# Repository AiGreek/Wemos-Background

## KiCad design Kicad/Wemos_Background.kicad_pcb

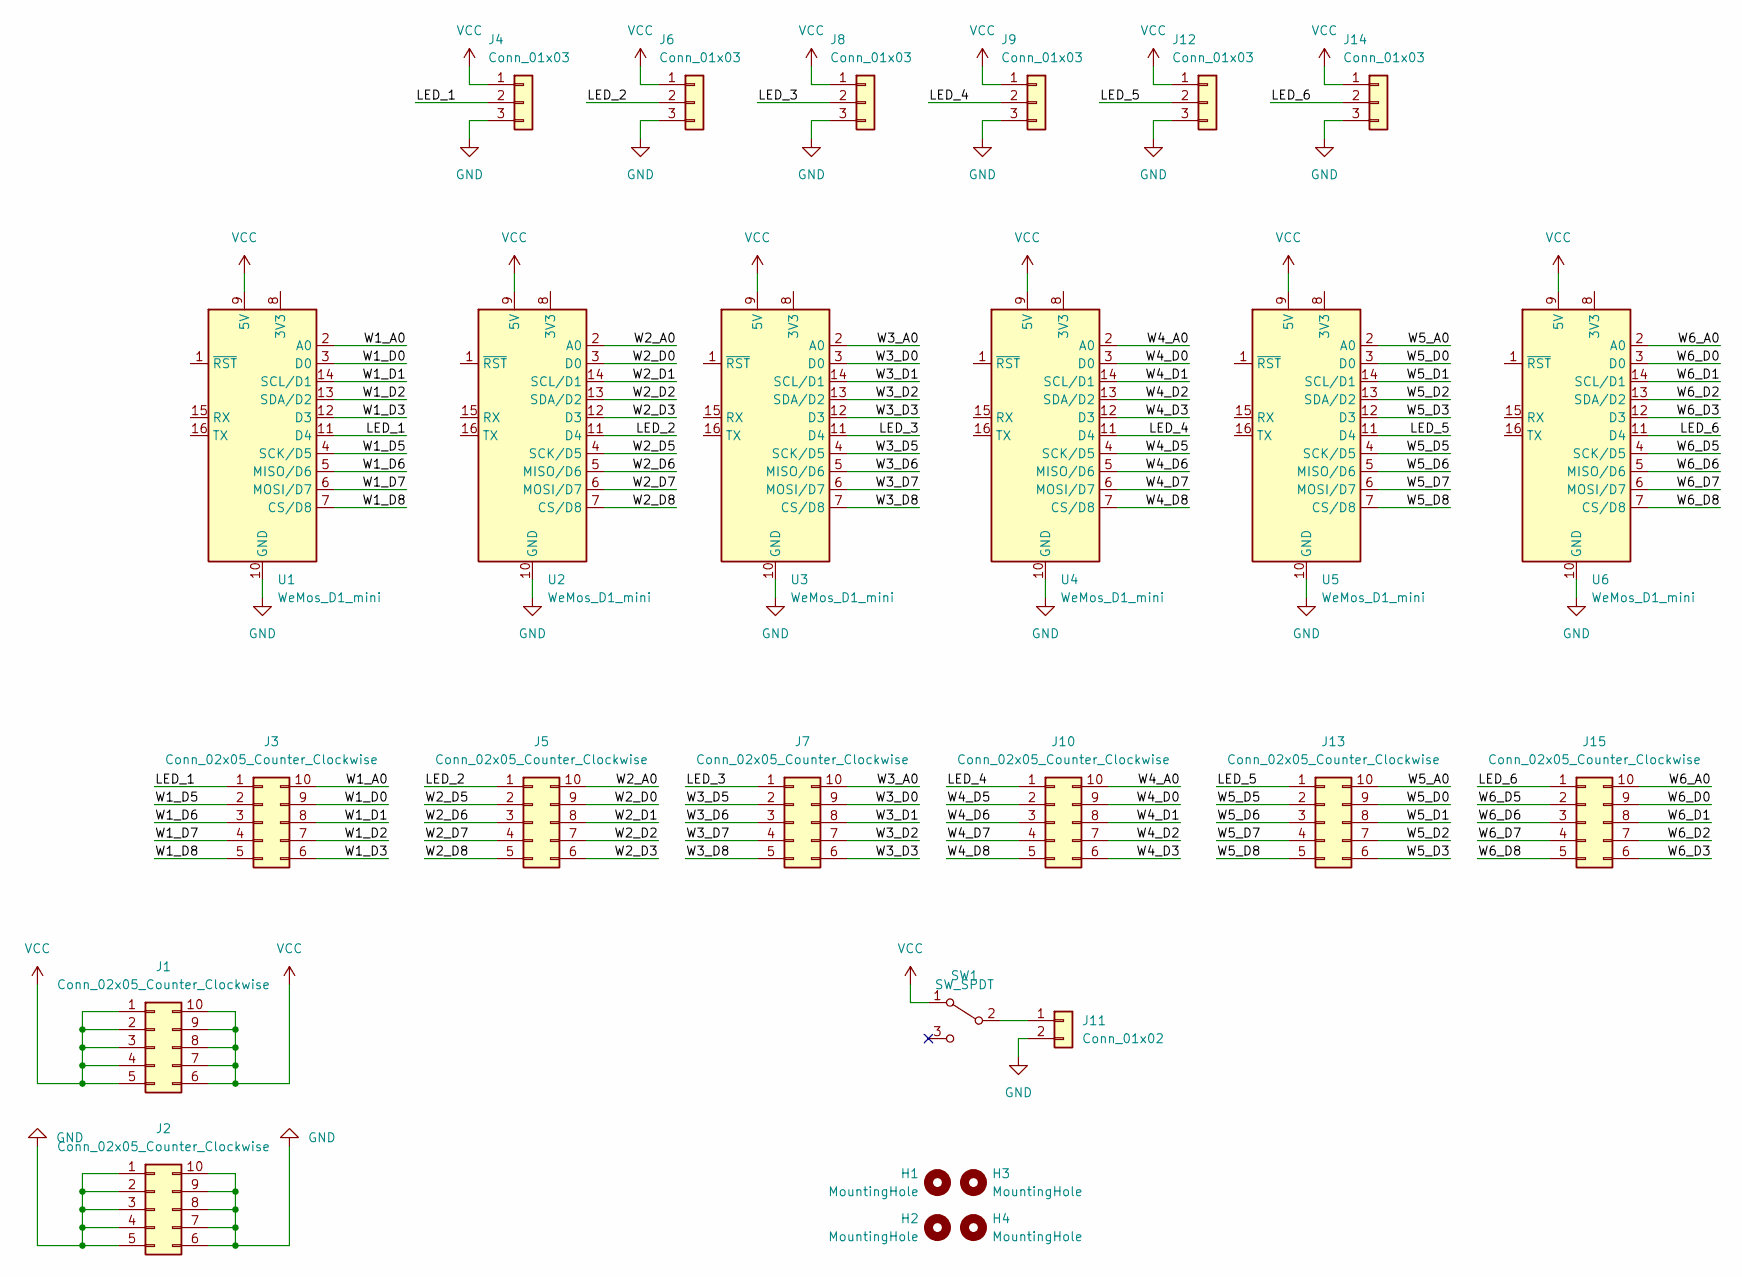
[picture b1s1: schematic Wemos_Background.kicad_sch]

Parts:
H1, H2, H3, H4: MountingHole; MountingHole_2.5mm_Pad
J1, J2, J3, J5, J7, J10, J13, J15: Conn_02x05_Counter_Clockwise; PinHeader_2x05_P2.54mm_Vertical
J4, J6, J8, J9, J12, J14: Conn_01x03; TerminalBlock_bornier-3_P5.08mm
J11: Conn_01x02; TerminalBlock_Altech_AK300-2_P5.00mm
SW1: SW_SPDT; SW_Slide_1P2T_CK_OS102011MS2Q
U1, U2, U3, U4, U5, U6: WeMos_D1_mini; WEMOS_D1_mini_light

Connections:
/LED_1: J3.1, J4.2, U1.11 (D4)
/LED_2: J5.1, J6.2, U2.11 (D4)
/LED_3: J7.1, J8.2, U3.11 (D4)
/LED_4: J9.2, J10.1, U4.11 (D4)
/LED_5: J12.2, J13.1, U5.11 (D4)
/LED_6: J14.2, J15.1, U6.11 (D4)
/W1_A0: J3.10, U1.2 (A0)
/W1_D0: J3.9, U1.3 (D0)
/W1_D1: J3.8, U1.14 (SCL/D1)
/W1_D2: J3.7, U1.13 (SDA/D2)
/W1_D3: J3.6, U1.12 (D3)
/W1_D5: J3.2, U1.4 (SCK/D5)
/W1_D6: J3.3, U1.5 (MISO/D6)
/W1_D7: J3.4, U1.6 (MOSI/D7)
/W1_D8: J3.5, U1.7 (CS/D8)
/W2_A0: J5.10, U2.2 (A0)
/W2_D0: J5.9, U2.3 (D0)
/W2_D1: J5.8, U2.14 (SCL/D1)
/W2_D2: J5.7, U2.13 (SDA/D2)
/W2_D3: J5.6, U2.12 (D3)
/W2_D5: J5.2, U2.4 (SCK/D5)
/W2_D6: J5.3, U2.5 (MISO/D6)
/W2_D7: J5.4, U2.6 (MOSI/D7)
/W2_D8: J5.5, U2.7 (CS/D8)
/W3_A0: J7.10, U3.2 (A0)
/W3_D0: J7.9, U3.3 (D0)
/W3_D1: J7.8, U3.14 (SCL/D1)
/W3_D2: J7.7, U3.13 (SDA/D2)
/W3_D3: J7.6, U3.12 (D3)
/W3_D5: J7.2, U3.4 (SCK/D5)
/W3_D6: J7.3, U3.5 (MISO/D6)
/W3_D7: J7.4, U3.6 (MOSI/D7)
/W3_D8: J7.5, U3.7 (CS/D8)
/W4_A0: J10.10, U4.2 (A0)
/W4_D0: J10.9, U4.3 (D0)
/W4_D1: J10.8, U4.14 (SCL/D1)
/W4_D2: J10.7, U4.13 (SDA/D2)
/W4_D3: J10.6, U4.12 (D3)
/W4_D5: J10.2, U4.4 (SCK/D5)
/W4_D6: J10.3, U4.5 (MISO/D6)
/W4_D7: J10.4, U4.6 (MOSI/D7)
/W4_D8: J10.5, U4.7 (CS/D8)
/W5_A0: J13.10, U5.2 (A0)
/W5_D0: J13.9, U5.3 (D0)
/W5_D1: J13.8, U5.14 (SCL/D1)
/W5_D2: J13.7, U5.13 (SDA/D2)
/W5_D3: J13.6, U5.12 (D3)
/W5_D5: J13.2, U5.4 (SCK/D5)
/W5_D6: J13.3, U5.5 (MISO/D6)
/W5_D7: J13.4, U5.6 (MOSI/D7)
/W5_D8: J13.5, U5.7 (CS/D8)
/W6_A0: J15.10, U6.2 (A0)
/W6_D0: J15.9, U6.3 (D0)
/W6_D1: J15.8, U6.14 (SCL/D1)
/W6_D2: J15.7, U6.13 (SDA/D2)
/W6_D3: J15.6, U6.12 (D3)
/W6_D5: J15.2, U6.4 (SCK/D5)
/W6_D6: J15.3, U6.5 (MISO/D6)
/W6_D7: J15.4, U6.6 (MOSI/D7)
/W6_D8: J15.5, U6.7 (CS/D8)
GND: J2.1, J2.2, J2.3, J2.4, J2.5, J2.6, J2.7, J2.8, J2.9, J2.10, J4.3, J6.3, J8.3, J9.3, J11.2, J12.3, J14.3, U1.10 (GND), U2.10 (GND), U3.10 (GND), U4.10 (GND), U5.10 (GND), U6.10 (GND)
unnamed: J11.1, SW1.2 (B)
VCC: J1.1, J1.2, J1.3, J1.4, J1.5, J1.6, J1.7, J1.8, J1.9, J1.10, J4.1, J6.1, J8.1, J9.1, J12.1, J14.1, SW1.1 (A), U1.9 (5V), U2.9 (5V), U3.9 (5V), U4.9 (5V), U5.9 (5V), U6.9 (5V)

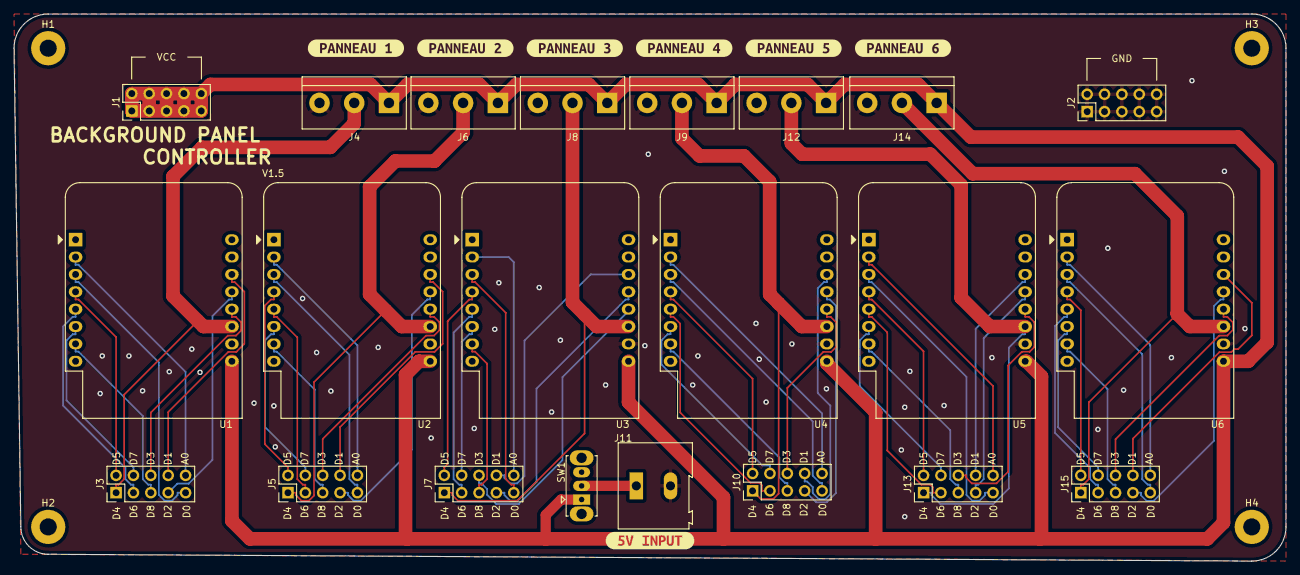
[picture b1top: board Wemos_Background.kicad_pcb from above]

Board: 2 copper layers, 186.0 x 80.0 mm, 33 parts (0 on the bottom side), 63 nets.

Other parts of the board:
kibuzzard-61C0C1A2: G***; kibuzzard-61C0C1A2
kibuzzard-61C0C1AB: G***; kibuzzard-61C0C1AB
kibuzzard-61C0C1B5: G***; kibuzzard-61C0C1B5
kibuzzard-61C0C1C1: G***; kibuzzard-61C0C1C1
kibuzzard-61C0C16B: G***; kibuzzard-61C0C16B
kibuzzard-61C0C17C: G***; kibuzzard-61C0C17C
kibuzzard-61C0C198: G***; kibuzzard-61C0C198
